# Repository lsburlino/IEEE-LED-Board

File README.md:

# IEEE LED Matrix Board

A KiCad hardware design for an 7-Segment LED matrix display board, built for a University of Portland IEEE student workshop. The board uses an Arduino Nano R4 MCU and a MAX7219 LED driver to control multiple LED display modules.

## Circuit Overview

| Component | Description |
|-----------|-------------|
| Arduino Nano R4 | Main microcontroller |
| MAX7219 | 8-digit serial LED display driver (Maxim Integrated) |
| TDCR1060M (x2) | Vishay LED display units |
| VS-1213-67-160GF (x3) | 12mm tactile input switches |

The design supports multiple voltage rails (1V, 3.3V, 5V) and uses passive components for current limiting and decoupling.

## Project Status

- [x] Schematic design
- [ ] PCB layout
- [ ] Firmware
- [ ] Fabrication

## Tools

- [KiCad 9.0](https://www.kicad.org/) — Schematic and PCB design

## Getting Started

1. Install [KiCad 9.0](https://www.kicad.org/download/) or later
2. Clone this repository
3. Open `LedMatrix.kicad_pro` in KiCad

## License

This project is developed by Luca Sburlino. Contact the maintainers for usage terms.

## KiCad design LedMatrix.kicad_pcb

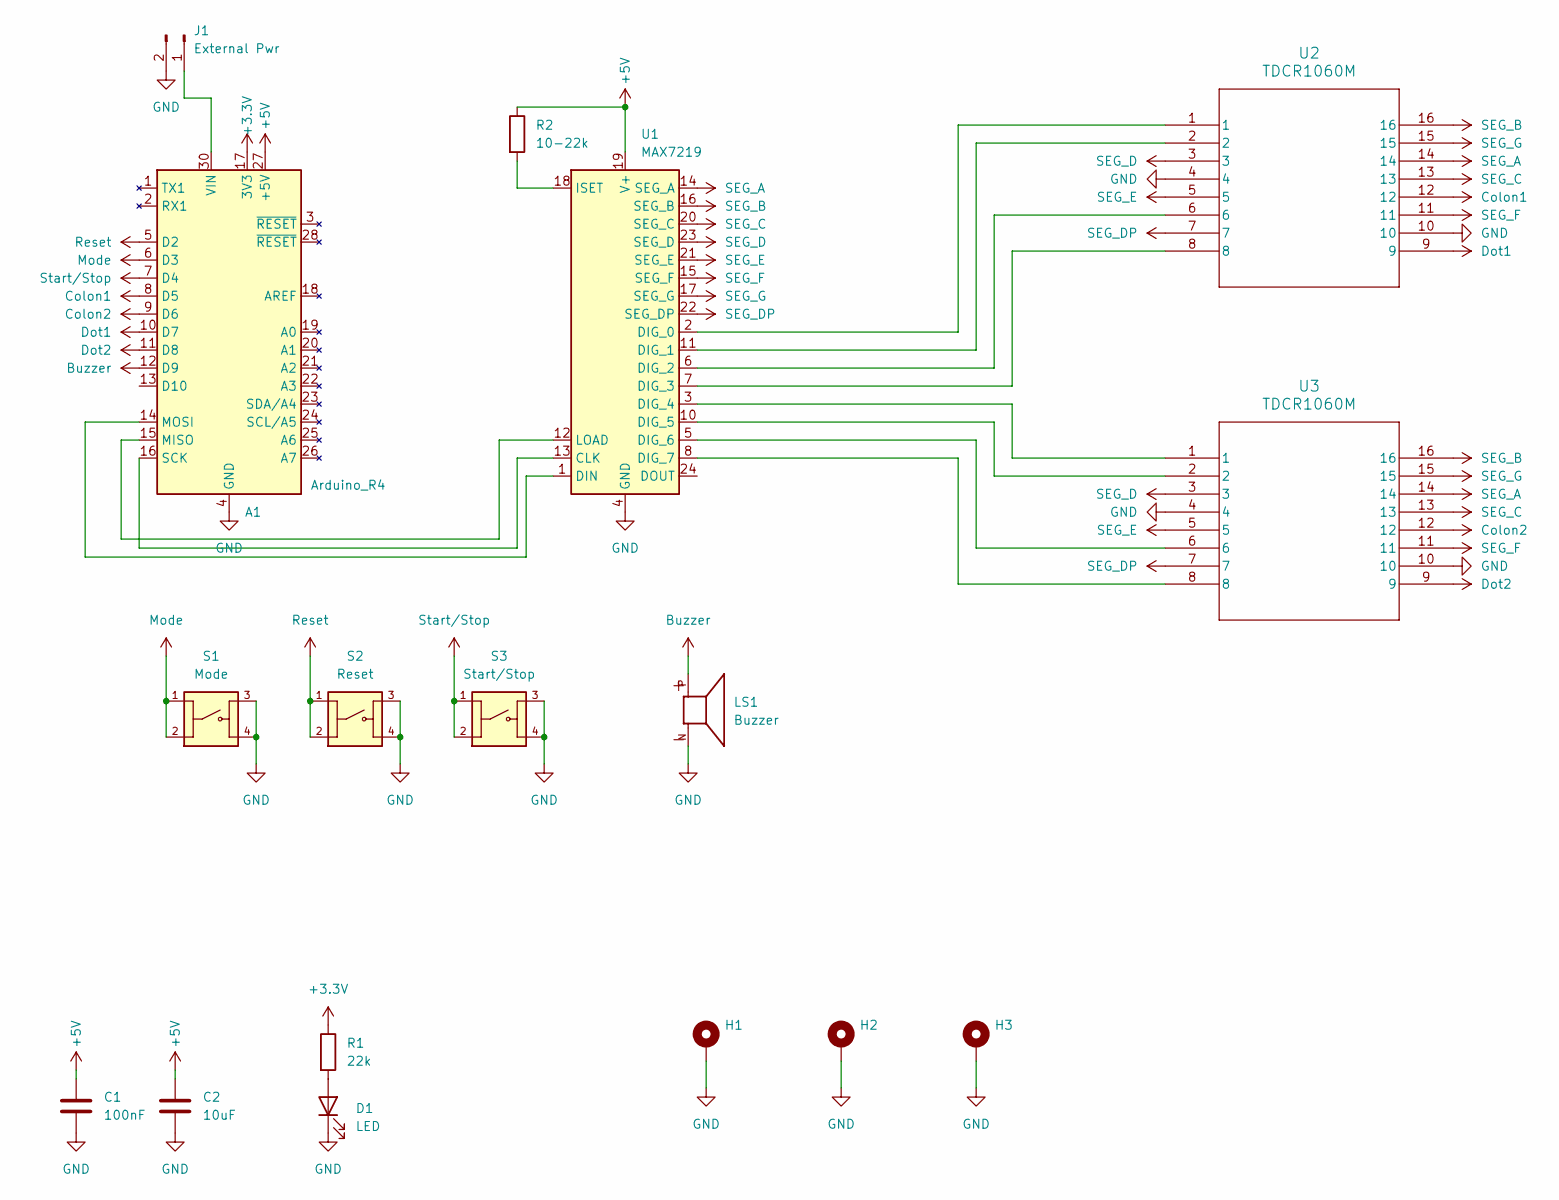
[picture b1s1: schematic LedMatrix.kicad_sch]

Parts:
A1: Arduino_R4; Arduino_Nano
C1: 100nF; C_0805_2012Metric_Pad1.18x1.45mm_HandSolder
C2: 10uF; CAP_YX_5X11_RUB
D1: LED; D_0805_2012Metric_Pad1.15x1.40mm_HandSolder
H1, H2, H3: MountingHole_Pad; MountingHole_3.2mm_M3_DIN965_Pad
J1: External Pwr; PinHeader_1x02_P2.54mm_Vertical
LS1: Buzzer; PARTREV 2014/07/25; DigiKey_Part_Number 668-1470-ND
R1: 22k; R_1206_3216Metric_Pad1.30x1.75mm_HandSolder
R2: 10-22k; R_1206_3216Metric_Pad1.30x1.75mm_HandSolder
S1: Mode; SW_VS-1213-67-160GF; PARTREV N/A
S2: Reset; SW_VS-1213-67-160GF; PARTREV N/A
S3: Start/Stop; SW_VS-1213-67-160GF; PARTREV N/A
U1: MAX7219; 21-0043D_24_MXM
U2, U3: TDCR1060M; TDCG1060M_VIS

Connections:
+3.3V: A1.17 (3V3), R1.1
+5V: A1.27 (+5V), C1.1, C2.1, R2.1, U1.19 (V+)
Buzzer: A1.12 (D9), LS1.P
Colon1: A1.8 (D5), U2.12
Colon2: A1.9 (D6), U3.12
Dot1: A1.10 (D7), U2.9
Dot2: A1.11 (D8), U3.9
GND: A1.4 (GND), A1.29 (GND), C1.2, C2.2, D1.1 (K), H1.1, H2.1, H3.1, J1.2, LS1.N, S1.3, S1.4, S2.3, S2.4, S3.3, S3.4, U1.4 (GND), U1.9 (GND), U2.4, U2.10, U3.4, U3.10
Mode: A1.6 (D3), S1.1, S1.2
unnamed: A1.15 (MISO), U1.12 (LOAD)
unnamed: A1.14 (MOSI), U1.1 (DIN)
unnamed: A1.16 (SCK), U1.13 (CLK)
unnamed: A1.30 (VIN), J1.1
unnamed: D1.2 (A), R1.2
unnamed: U1.2 (DIG_0), U2.1
unnamed: U1.11 (DIG_1), U2.2
unnamed: U1.6 (DIG_2), U2.6
unnamed: U1.7 (DIG_3), U2.8
unnamed: U1.3 (DIG_4), U3.1
unnamed: U1.10 (DIG_5), U3.2
unnamed: U1.5 (DIG_6), U3.6
unnamed: U1.8 (DIG_7), U3.8
unnamed: R2.2, U1.18 (ISET)
Reset: A1.5 (D2), S2.1, S2.2
SEG_A: U1.14 (SEG_A), U2.14, U3.14
SEG_B: U1.16 (SEG_B), U2.16, U3.16
SEG_C: U1.20 (SEG_C), U2.13, U3.13
SEG_D: U1.23 (SEG_D), U2.3, U3.3
SEG_DP: U1.22 (SEG_DP), U2.7, U3.7
SEG_E: U1.21 (SEG_E), U2.5, U3.5
SEG_F: U1.15 (SEG_F), U2.11, U3.11
SEG_G: U1.17 (SEG_G), U2.15, U3.15
Start/Stop: A1.7 (D4), S3.1, S3.2

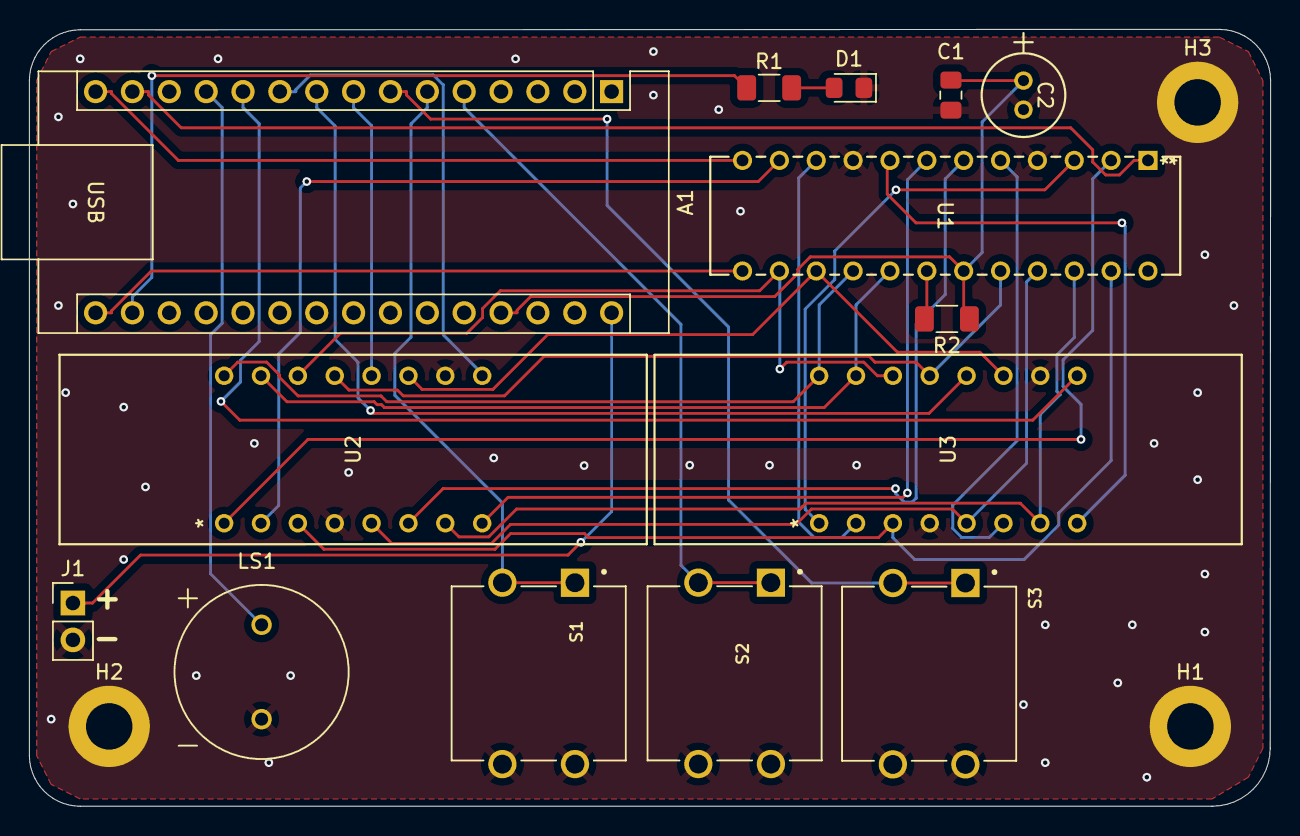
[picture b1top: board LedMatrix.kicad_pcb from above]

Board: 2 copper layers, 85.5 x 53.5 mm, 17 parts (0 on the bottom side), 33 nets.
